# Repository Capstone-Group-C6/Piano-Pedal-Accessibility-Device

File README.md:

# Piano-Pedal-Accessibility-Device (PianoPAD)
Northeastern University 1st Place Capstone 2023 Open Source Repository for our PianoPAD system. Software designed by Roberto Chadwick, Lucas Laya Marina, and Luke Wisner. Hardware designed by Hanchen Liu, Josh Moffat, and Tristan Siu.

### General Overview
This project provides a way for people with a disability to use their piano pedals by tracking their head tilt and replicating it as pedal presses. The app is only for iOS devices, as we used Apple's Vision Library to get the necessary head tracking data. We wanted to make our work open-source so that anyone could make this device for themselves or anyone they know who would like the ability to use their piano pedals. Through the device that you plug into the piano port and the iOS application, we have created a system that can replicate pedal presses for one or three pedals. 

This idea began as a way to help Jonathan Goodwin for our engineering capstone project. Jonathan is a retired stunt performer and a current keynote speaker. Follow him at: https://www.instagram.com/jonathangoodwinofficial/?hl=en

Jonathan loves to play the piano, but he is unable to use the pedals because he was paralyzed from the waist down in an accident. We set out to create a device that would allow him to once again get full use from his piano. Through our initial meetings with Jonathan, we were able to discern the simplest, most intuitive way to make that possible: using the tilt of his head. The solutions that exist today all require the user to bite down on or blow into a device, but that would prevent Jonathan from being able to sing when he plays. The head tilt became the perfect solution because it fixed this issue while remaining intuitive to the user.

## Hardware
### Hardware Overview
One half of the PianoPAD system is the device that plugs into the back of the piano and replicates the pedal press signal. Anyone who wants to use this design in the future will need a chip capable of sending and recieving data over bluetooth (we used an ESP32 as a relatively inexpensive option so our schematics match that). In addition, they will need a way to power the device through micro-USB and connect the device to their piano pedal port using 1/4-inch jacks.

### Hardware Replication
The necessary KiCad files (schematic and PCB layout) have been added to allow anyone to replicate our board for their own personal use. The following images display the schematic design as well as the PCB layout of the components and traces involved in integrating all the parts of the board. 

In terms of the manufacturing and assembly process, orders can be made through various PCB manufacturers (we used JLCPCB.com) and provide them with our PCB/schematic files to make an order. Below is the part list with links to sites to purchase each component. (NOTE: You can also import the provided files into the KiCad project manager to view/make any changes to the project) In terms of assembly, be sure to solder on the components that are not already assembled onto the board from the manufacturer (i.e. 1/4" sockets...).

Parts List:
- 1/4" Socket: https://www.amazon.com/dp/B07MR2TT3Q?psc=1&smid=A34H4GNHCXU7L2&ref_=chk_typ_imgToDp
- LEDs: (https://www.amazon.com/eBoot-Pieces-Emitting-Diodes-Assorted/dp/B06XPV4CSH/ref=sr_1_8?crid=1UQGUEZ7QY5KU&keywords=leds&qid=1701737252&sprefix=leds%2Caps%2C88&sr=8-8&th=1)
- ESP32 Chip: [https://www.amazon.com/Development-Microcontroller-Integrated-Antenna-Amplifiers/dp/B09GK74F7N/ref=sr_1_1_sspa?crid=18ESI34J05HVB&keywords=esp32&qid=1701737319&sprefix=esp32%2Caps%2C82&sr=8-1-spons&sp_csd=d2lkZ2V0TmFtZT1zcF9hdGY&psc=1](https://www.amazon.com/Espressif-ESP32-S3-WROOM-1U-ESP32-S3-WROOM-1U-N8R8-Module/dp/B0B8NWF4F5/ref=sr_1_3?crid=3B4YTQOZYAYG1&keywords=esp32%2Bwroom%2B1u&qid=1701827727&sprefix=esp32%2Bwroom%2B1u%2Caps%2C95&sr=8-3&th=1)

### Three Pedal Proprietary Cable
Using three pedals with the device is a little more complicated because of how digital pianos are made. Any piano that can have a three-pedal attachment makes that connection through a proprietary cable instead of a standard 1/4-inch jack, so it was impossible to design a one-size-fits-all solution. Any users who want to use this functionality will have to create their own cable that ends in three 1/4-inch jacks to connect to the device. That way the other end of that cable can be the proper connection port that will work for their specific piano.

## Software
### Software Overview
The other half of the PianoPAD system is the iOS application that detects the head tilt and sends the signal over Bluetooth to the device. The app can be pushed to a TestFlight app for sharing with others, or the user can build directly to their phone through XCode. The app contains settings for selecting one or three pedals, changing the tilt direction, adjusting the threshold angle that triggers the tilt, toggling hold, and toggling inverse. The app has an additional page to give the user some directions on how to connect to the device through Bluetooth, and the best way to orient the phone when beginning a session. When the session view is started, it takes all of the saved data from settings, tracks the user's face, and begins sending data to the device to replicate the signal of the pedal press.

### Firmware Overview
The firmware that needs to be uploaded to the ESP32 chip also exists within this repository. It activates the necessary GPIO pins when it receives the packet from the application and it also contains the code necessary to establish the Bluetooth connection. The firmware then reads the sent byte to determine if any of the pedals are held down and which GPIO pins are activated if so.

### Bluetooth Connection
As stated above, the device establishes a connection when it is powered on, and the app with the corresponding UUID will be what it connects to. When the session is started in the app, it begins sending bytes where the last 3 bits trigger which pedals are currently being held down. 

### Head Tracking
The head tracking uses Apple's Vision Library to isolate features on the face and then return facial position data. This data includes the roll (tilting head side to side) and the pitch (tilting head up and down) in radians which allow us to determine the angle from the center position. The session tracks if the input radian threshold has been passed using this data, and that determines what data we send to the device to press the correct pedal. There is also a debounce implemented to prevent data flip-flopping when the user keeps their head right on the threshold. Additionally, the polling rate of the data is based on how new the iOS device is. The newer the device the smoother it will function, and we don't recommend running this system on anything older than an iPhone X.

### Navigating Settings
The settings page in the top right corner of the app allows the user to adjust what feels best to them when the session is running. There are two tabs for one pedal and three-pedal, which determines if the session will try to detect one or three directions. In the one pedal tab, the user has the ability to determine which way they want to tilt their head to pass the threshold, either left, right, both, or down. In addition, there are options to toggle inverse which presses the pedal unless the threshold is crossed, and toggle hold which keeps the state of the pedal when the threshold is crossed. There is a slider to adjust the angle with an example threshold bar beneath so that the user can test that angle and see what feels best for them. It was important to us to give the user as much freedom as possible to configure their sessions however they wanted to be natural for them.

In the three-pedal system, the same options are available, except for the ability to hold and change directions for each pedal. The sustain and sostenuto pedals can have their directions switched to change which one is left and right, but the soft pedal is locked as tilting downward. This is because when playing the piano, the soft pedal is the only other pedal that can be used in tandem with the other two. Given that you can't tilt your head both left and right at the same time, but you can tilt down and right, we decided to keep the soft pedal as only down. Each of these three pedals has the ability to be active or inactive, so if a song doesn't require a specific pedal, you can turn it off to avoid triggering it by accident. These pedals also all have angle adjustment sliders and threshold bars to give the user a visual of what angles would work best for them.

When the session begins, the saved settings variables are processed between specified cases that run the head-tracking logic. There is a case to handle every possible combination of toggles and angle values in both the one and three-pedal systems. The user can then see these settings in action through the indicator bars in the session view. There are the same threshold bars to show how far the user's head is tilting, and at the bottom, there are indicator bars to show which pedals are activated and sending a signal to the device.

### Software Replication
To replicate the software, the user will need to flash the firmware onto the chip they have started using. From there, the app can be run through XCode with no additional changes and be built into an iPhone for testing. Additionally, if the user wants to share the app with others, they can get an Apple Developer License and push the app to TestFlight where it can be downloaded on any iOS device. The backend functions that deal with Bluetooth connection and face tracking can be found in the model, and all of the frontend app pages can be found in the view. 

## Additional Implementations 
Another reason that we wanted to make this code publicly available is that it has so many other applications to help anyone with disabilities. We designed the app with a piano in mind, but the code can be repurposed to work with another instrument such as a guitar or drumset. Further beyond this, the head tracking functions could be expanded upon to communicate with non-instrument devices like a wheelchair. We hope that this code can help any who uses it!

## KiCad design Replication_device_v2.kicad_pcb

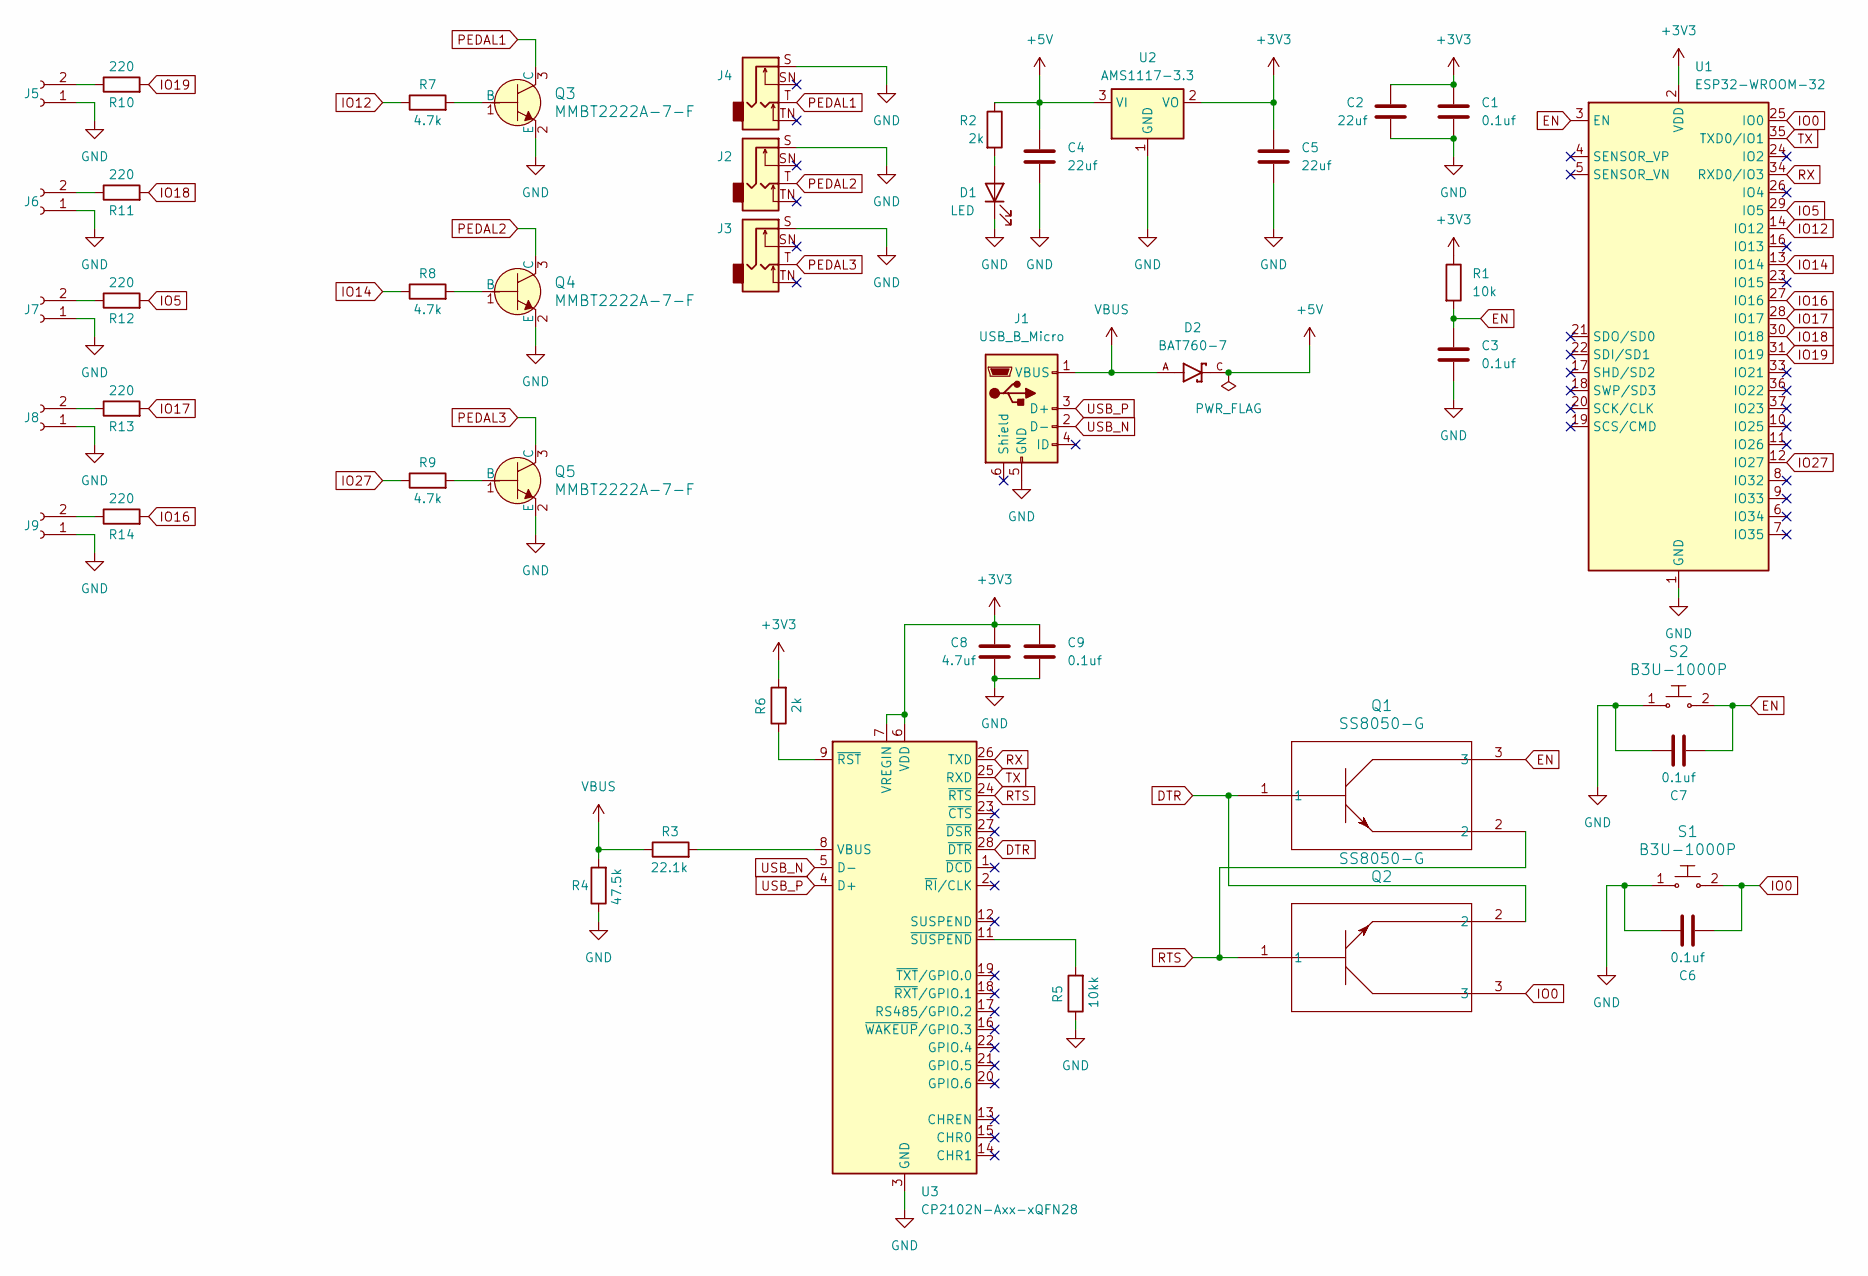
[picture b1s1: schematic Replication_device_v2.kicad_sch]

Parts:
C1, C3, C6, C7, C9: 0.1uf; C_0402_1005Metric
C2, C4, C5: 22uf; C_0603_1608Metric
C8: 4.7uf; C_0402_1005Metric
D1: LED; LED_0603_1608Metric
D2: BAT760-7; SOD2513X120N; PARTREV 9-2
J1: USB_B_Micro; USB_Micro-B_Molex_47346-0001
J2, J3, J4: AudioJack2_Switch; Jack_6.35mm_Neutrik_NMJ4HCD2_Horizontal
J5, J6, J7, J8, J9: Conn_01x02_Socket; SolderWire-0.5sqmm_1x02_P4.6mm_D0.9mm_OD2.1mm
Q1, Q2: SS8050-G; TRAN_SS8050-G_CIP
Q3, Q4, Q5: MMBT2222A-7-F; SOT-23-3; MPN MMBT2222A-7-F; Digi-Key_PN MMBT2222A-FDICT-ND
R1: 10k; R_0402_1005Metric
R2, R6: 2k; R_0402_1005Metric
R3: 22.1k; R_0402_1005Metric
R4: 47.5k; R_0402_1005Metric
R5: 10kk; R_0402_1005Metric
R7, R8, R9: 4.7k; R_0402_1005Metric
R10, R11, R12, R13, R14: 220; R_0402_1005Metric
S1, S2: B3U-1000P; SW_Push_1P1T_XKB_TS-1187A; MPN B3U-1000P; Digi-Key_PN SW1020CT-ND
U1: ESP32-WROOM-32
U2: AMS1117-3.3; SOT-223-3_TabPin2
U3: CP2102N-Axx-xQFN28; QFN-28-1EP_5x5mm_P0.5mm_EP3.35x3.35mm

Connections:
+3V3: C1.1, C2.1, C5.1, C8.1, C9.1, R1.1, R6.2, U1.2 (VDD), U2.2 (VO), U3.6 (VDD), U3.7 (VREGIN)
+5V: C4.1, D2.C, R2.1, U2.3 (VI)
DTR: Q1.1, Q2.2, U3.28 (~DTR)
EN: C3.1, C7.2, Q1.3, R1.2, S2.2, U1.3 (EN)
GND: C1.2, C2.2, C3.2, C4.2, C5.2, C6.1, C7.1, C8.2, C9.2, D1.1 (K), J1.5 (GND), J2.S, J3.S, J4.S, J5.1, J6.1, J7.1, J8.1, J9.1, Q3.2 (E), Q4.2 (E), Q5.2 (E), R4.1, R5.1, S1.1, S2.1, U1.1 (GND), U1.15 (GND), U1.38 (GND), U1.39 (GND), U2.1 (GND), U3.3 (GND), U3.29 (GND)
IO0: C6.2, Q2.3, S1.2, U1.25 (IO0)
IO5: R12.2, U1.29 (IO5)
IO12: R7.1, U1.14 (IO12)
IO14: R8.1, U1.13 (IO14)
IO16: R14.2, U1.27 (IO16)
IO17: R13.2, U1.28 (IO17)
IO18: R11.2, U1.30 (IO18)
IO19: R10.2, U1.31 (IO19)
IO27: R9.1, U1.12 (IO27)
unnamed: D1.2 (A), R2.2
unnamed: J5.2, R10.1
unnamed: J6.2, R11.1
unnamed: J7.2, R12.1
unnamed: J8.2, R13.1
unnamed: J9.2, R14.1
unnamed: Q3.1 (B), R7.2
unnamed: Q4.1 (B), R8.2
unnamed: Q5.1 (B), R9.2
unnamed: R3.2, U3.8 (VBUS)
unnamed: R6.1, U3.9 (~RST)
unnamed: R5.2, U3.11 (~SUSPEND)
PEDAL1: J4.T, Q3.3 (C)
PEDAL2: J2.T, Q4.3 (C)
PEDAL3: J3.T, Q5.3 (C)
RTS: Q1.2, Q2.1, U3.24 (~RTS)
RX: U1.34 (RXD0/IO3), U3.26 (TXD)
TX: U1.35 (TXD0/IO1), U3.25 (RXD)
USB_N: J1.2 (D-), U3.5 (D-)
USB_P: J1.3 (D+), U3.4 (D+)
VBUS: D2.A, J1.1 (VBUS), R3.1, R4.2

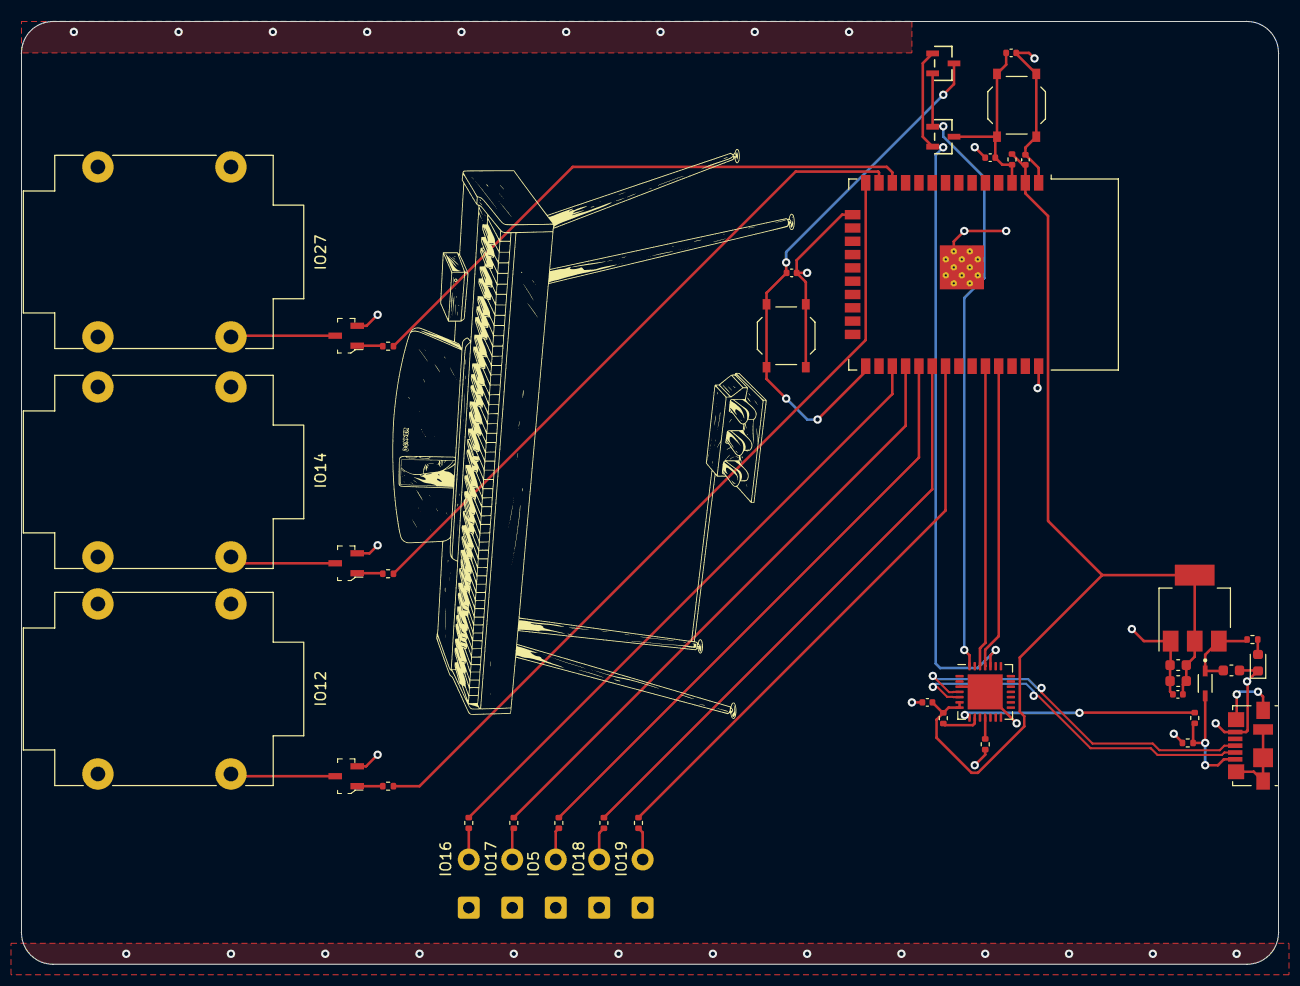
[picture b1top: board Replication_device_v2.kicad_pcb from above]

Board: 2 copper layers, 120.0 x 90.0 mm, 44 parts (0 on the bottom side), 35 nets.

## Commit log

2023-12-04 Update README.md
    Create README sections to be filled with relevant info
2023-12-05 Update README.md
    Added additional README info for general overviews and additional applications
2023-12-05 Add files via upload
    Added schematic files for recreating the PPAD device
2023-12-05 Added all app files, organized hardware files, and attached Piano logos
2023-12-05 Update README.md
    Added Hardware info with relevant pictures
2023-12-05 Update README.md
    Finished initial software portion of README explanation
2023-12-05 Adding pictures to file structure
2023-12-05 Updated folder name for ease of use
2023-12-05 Update README.md
    Added app example images to README
2023-12-05 Added homepage view
2023-12-05 Update README.md
    Added homepage view
2023-12-06 Update README.md
    Updated ESP32 chip link, some small text errors fixed
2023-12-08 Update SessionView.swift
    added debouncing comments
2023-12-08 Final Firmware
    Firmware
2023-12-08 Update README.md
    Works with either way after final firmware
2023-12-08 Update README.md
    bc we are winners :)
2023-12-08 Delete SoftwareFiles/.DS_Store
    deleted mac meta data
2023-12-08 Delete SoftwareFiles/PPAD/.DS_Store
    deleted mac metadata
2023-12-08 Delete SoftwareFiles/PPAD/Assets.xcassets/.DS_Store
    removed metadata
2023-12-08 Updated Folder Name
2023-12-08 Update README.md
    removed identifier after UUID
2023-12-09 Update README.md
    Changed PPAD to PianoPAD as discussed before the presentation
2024-01-02 Improved code structure
2024-01-02 Added abstracted functionality to improve code
2024-01-02 Removed comment
